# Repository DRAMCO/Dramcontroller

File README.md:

# Dramcontroller
HID controller board design for Engineering Experience 2.
The peripherals with corresponding pins are described below. 
A distinction is made between the on-board peripherals, I2C addresses and sensor slots

## On-board peripherals
| Peripherals | Corresponding GPIO Pin  |
|---|---|
| Buzzer | 2 |
| Vibrator 1 | 12 |
| Vibrator 2 | 5 |
| Debug LED | 13 |
| IO Expender INT | 11 |

## I2C addresses
Four IO expanders connected with the I2C bus control the 7 segment displays, led indicator array and GPIO 3 from every sensor slot. I2C sensors should use always other addresses to prevent collisions during operation.

| IO Expander | Corresponding I2C addres  |
|---|---|
| Sensor slot GPIO 3 | 0x38 |
| Segment display 2 | 0x39 |
| Segment display 1 | 0x3A |
| Led array | 0x3B |

## Sensor slots
### Sensor slot 1
| Peripheral | Pin | Comment |
|---|---|---|
| GPIO 1 | 6 | Digital |
| GPIO 2 | 14  | Digital - Analog |
| GPIO 3 | IO EXP pin 1 | Digital (0b00000001) |
| UART  |  | Serial |
| I2C  |  |  |

### Sensor slot 2
| Peripheral | Pin | Comment |
|---|---|---|
| GPIO 1 | 39 | Digital |
| GPIO 2 | 15  | Digital - Analog |
| GPIO 3 | IO EXP pin 2 | Digital (0b00000010) |
| UART  |  | Serial |
| I2C  |  |  |

### Sensor slot 3
| Peripheral | Pin | Comment |
|---|---|---|
| GPIO 1 | 8 | Digital |
| GPIO 2 | 16  | Digital - Analog |
| GPIO 3 | IO EXP pin 3 | Digital (0b00000100) |
| UART  |  | Serial |
| I2C  |  |  |

### Sensor slot 4
| Peripheral | Pin | Comment |
|---|---|---|
| GPIO 1 | 9 | Digital |
| GPIO 2 | 17  | Digital - Analog |
| GPIO 3 | IO EXP pin 4 | Digital (0b00001000) |
| UART  |  | Serial |
| I2C  |  |  |

### Sensor slot 5
| Peripheral | Pin | Comment |
|---|---|---|
| GPIO 1 | 10 | Digital |
| GPIO 2 | 18  | Digital - Analog |
| GPIO 3 | IO EXP pin 5 | Digital (0b00010000) |
| UART  |  | Serial1 |
| I2C  |  |  |

### Sensor slot 6
| Peripheral | Pin | Comment |
|---|---|---|
| GPIO 1 | 23 | Digital |
| GPIO 2 | 19  | Digital - Analog |
| GPIO 3 | IO EXP pin 6 | Digital (0b00100000) |
| UART  |  | Serial1 |
| I2C  |  |  |

### Sensor slot 7
| Peripheral | Pin | Comment |
|---|---|---|
| GPIO 1 | 24 | Digital |
| GPIO 2 | 4  | Digital - Analog |
| GPIO 3 | IO EXP pin 7 | Digital (0b01000000) |
| UART  |  | Serial1 |
| I2C  |  |  |

### Sensor slot 8
| Peripheral | Pin | Comment |
|---|---|---|
| GPIO 1 | 22 | Digital |
| GPIO 2 | 3  | Digital - Analog |
| GPIO 3 | IO EXP pin 8 | Digital (0b10000000) |
| UART  |  | Serial1 |
| I2C  |  |  |

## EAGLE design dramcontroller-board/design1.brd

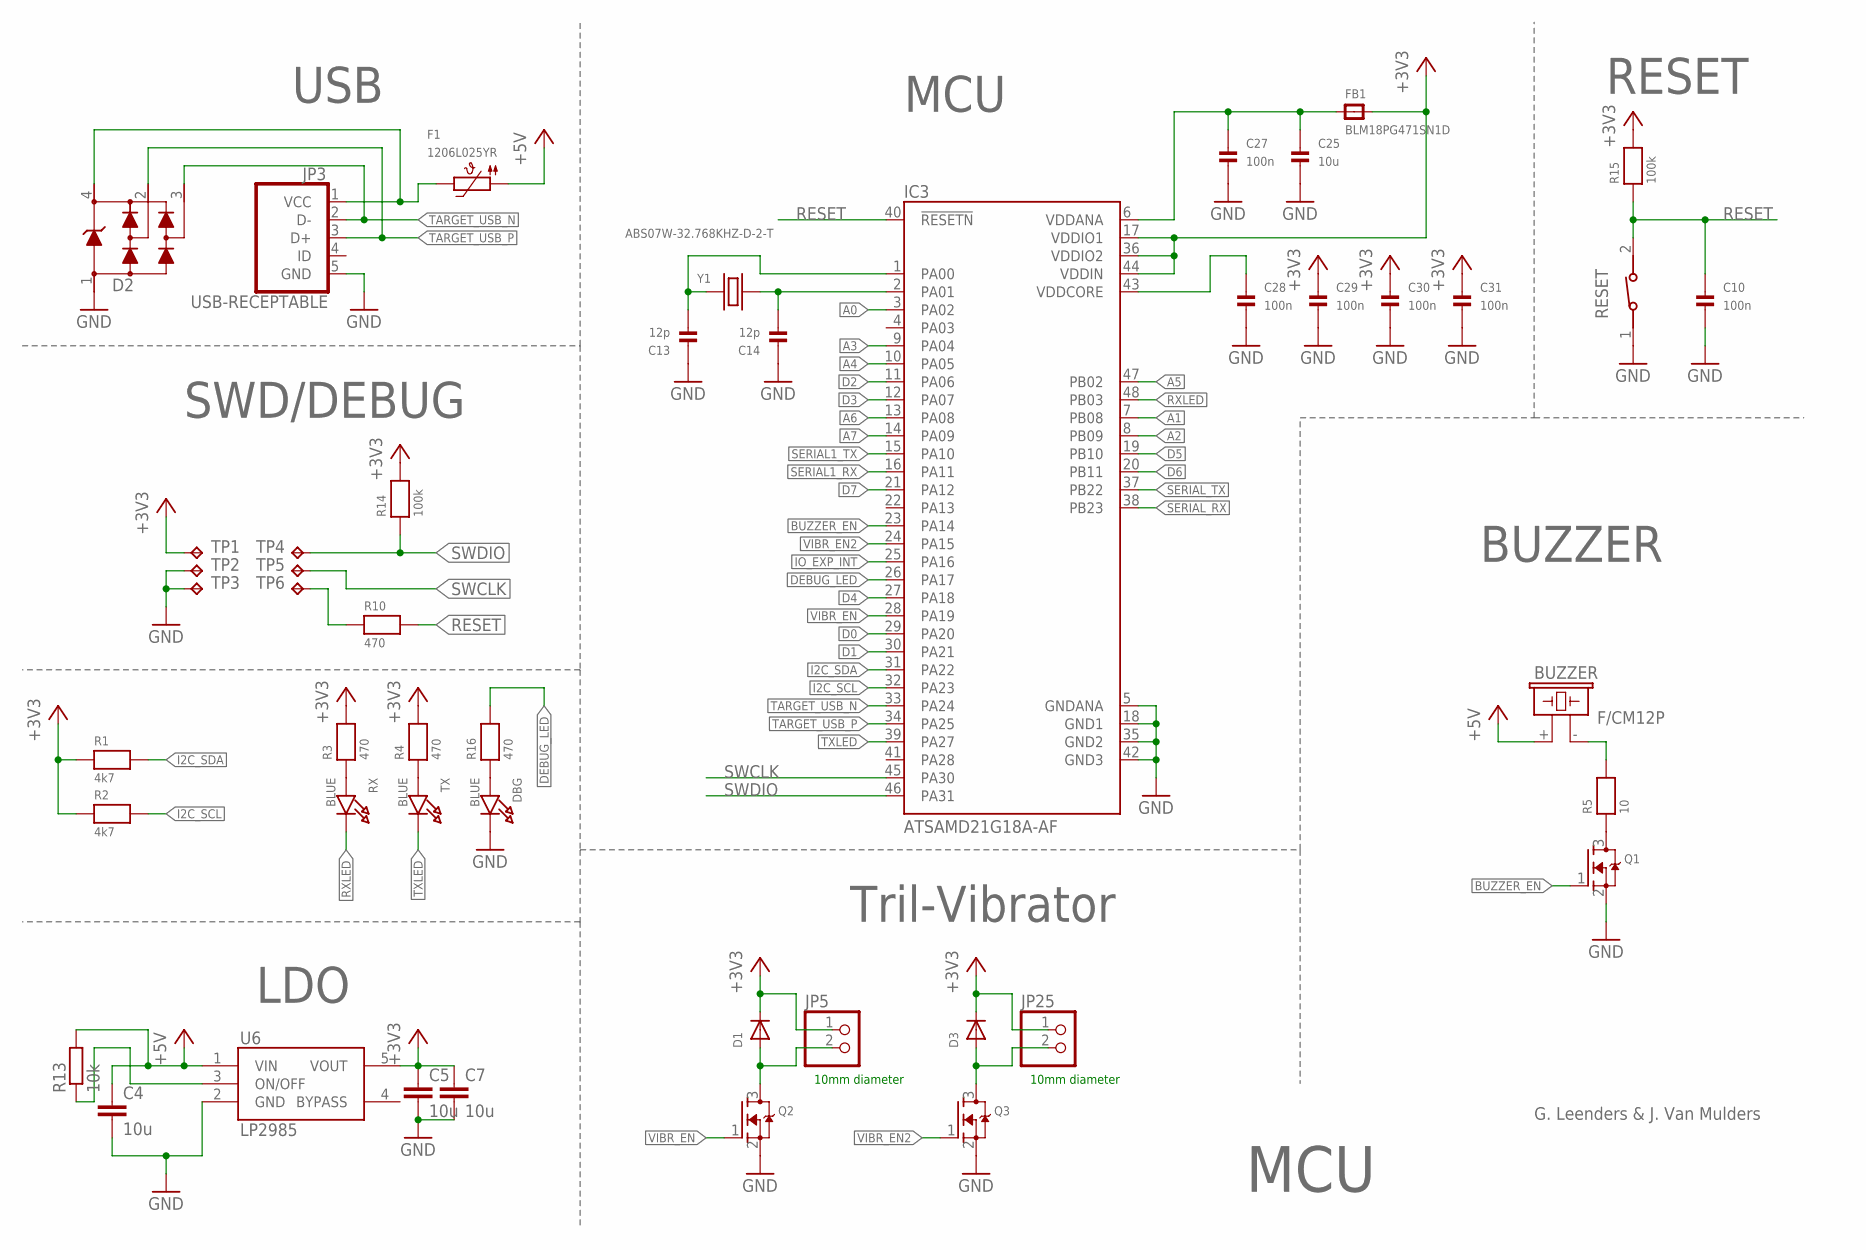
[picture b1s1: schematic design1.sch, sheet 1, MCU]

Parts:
BUZZER: F/CM12P
C4, C5, C7: 10u; C0805
C10, C27, C28, C29, C30, C31: 100n; 0603
C13, C14: 12p; 0603
C25: 10u; 0805
D1, D3: DIODESOD-123; SOD-123
D2: PRTR5V0U2X,215; SOT143B
DBG: BLUE; CHIPLED_0805
F1: 1206L025YR; 1206
FB1: BLM18PG471SN1D; _0603
IC3: ATSAMD21G18A-AF; QFP50P900X900X120-48N
JP3: USB-RECEPTABLE; FCI-10103594-0001LF
JP5, JP25: HEADER-1X2ROUND; 1X02_ROUND
Q1, Q2, Q3: MOSFET-NWIDE; SOT23-WIDE
R1, R2: 4k7; 0603
R3, R4, R10, R16: 470; 0603
R5: 10; 0603
R13: 10k; R0603
R14, R15: 100k; 0603
RESET: 434111043826
RX: BLUE; CHIPLED_0805
TP1, TP2, TP3, TP4, TP5, TP6: TPTP11R; TP11R
TX: BLUE; CHIPLED_0805
U6: LP2985AIM5-3.3; SOT25
Y1: ABS07W-32.768KHZ-D-2-T; XTAL320X150X90

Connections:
+3V3: C5.1, C7.1, C29.1, C30.1, C31.1, D1.C, D3.C, FB1.2, IC3.17 (VDDIO1), IC3.36 (VDDIO2), IC3.44 (VDDIN), JP5.1, JP25.1, R1.1, R2.1, R3.2, R4.2, R14.2, R15.2, TP1.TP, U6.5 (VOUT); also elsewhere on the board
+5V: BUZZER.+ (1), C4.1, F1.1, R13.2, U6.1 (VIN)
A0: IC3.3 (PA02); also elsewhere on the board
A1: IC3.7 (PB08); also elsewhere on the board
A2: IC3.8 (PB09); also elsewhere on the board
A3: IC3.9 (PA04); also elsewhere on the board
A4: IC3.10 (PA05); also elsewhere on the board
A5: IC3.47 (PB02); also elsewhere on the board
A6: IC3.13 (PA08); also elsewhere on the board
A7: IC3.14 (PA09); also elsewhere on the board
BUZZER_EN: IC3.23 (PA14), Q1.1 (G)
D0: IC3.29 (PA20); also elsewhere on the board
D1: IC3.30 (PA21); also elsewhere on the board
D2: IC3.11 (PA06); also elsewhere on the board
D3: IC3.12 (PA07); also elsewhere on the board
D4: IC3.27 (PA18); also elsewhere on the board
D5: IC3.19 (PB10); also elsewhere on the board
D6: IC3.20 (PB11); also elsewhere on the board
D7: IC3.21 (PA12); also elsewhere on the board
DEBUG_LED: IC3.26 (PA17), R16.2
GND: C4.2, C5.2, C7.2, C10.2, C13.1, C14.1, C25.2, C27.2, C28.2, C29.2, C30.2, C31.2, D2.1, DBG.C, IC3.5 (GNDANA), IC3.18 (GND1), IC3.35 (GND2), IC3.42 (GND3), JP3.5 (GND), Q1.2 (S), Q2.2 (S), Q3.2 (S), RESET.1, TP2.TP, TP3.TP, U6.2 (GND); also elsewhere on the board
I2C_SCL: IC3.32 (PA23), R2.2; also elsewhere on the board
I2C_SDA: IC3.31 (PA22), R1.2; also elsewhere on the board
IO_EXP_INT: IC3.25 (PA16); also elsewhere on the board
LDO_EN: R13.1, U6.3 (ON/OFF)
unnamed: R3.1, RX.A
unnamed: R4.1, TX.A
unnamed: BUZZER.- (2), R5.2
unnamed: C28.1, IC3.43 (VDDCORE)
unnamed: Q1.3 (D), R5.1
unnamed: C25.1, C27.1, FB1.1, IC3.6 (VDDANA)
unnamed: D2.4, F1.2, JP3.1 (VCC)
unnamed: D3.A, JP25.2, Q3.3 (D)
unnamed: C13.2, IC3.1 (PA00), Y1.1
unnamed: C14.2, IC3.2 (PA01), Y1.2
unnamed: DBG.A, R16.1
unnamed: R10.1, TP6.TP
unnamed: D1.A, JP5.2, Q2.3 (D)
RESET: C10.1, IC3.40 (!RESETN), R10.2, R15.1, RESET.2
RXLED: IC3.48 (PB03), RX.C
SERIAL1_RX: IC3.16 (PA11); also elsewhere on the board
SERIAL1_TX: IC3.15 (PA10); also elsewhere on the board
SERIAL_RX: IC3.38 (PB23); also elsewhere on the board
SERIAL_TX: IC3.37 (PB22); also elsewhere on the board
SWCLK: IC3.45 (PA30), TP5.TP
SWDIO: IC3.46 (PA31), R14.1, TP4.TP
TARGET_USB_N: D2.3, IC3.33 (PA24), JP3.2 (D-)
TARGET_USB_P: D2.2, IC3.34 (PA25), JP3.3 (D+)
TXLED: IC3.39 (PA27), TX.C
VIBR_EN: IC3.28 (PA19), Q2.1 (G)
VIBR_EN2: IC3.24 (PA15), Q3.1 (G)

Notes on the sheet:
10mm diameter
MCU
G. Leenders & J. Van Mulders
LDO
USB
SWD/DEBUG
RESET
BUZZER
Tril-Vibrator

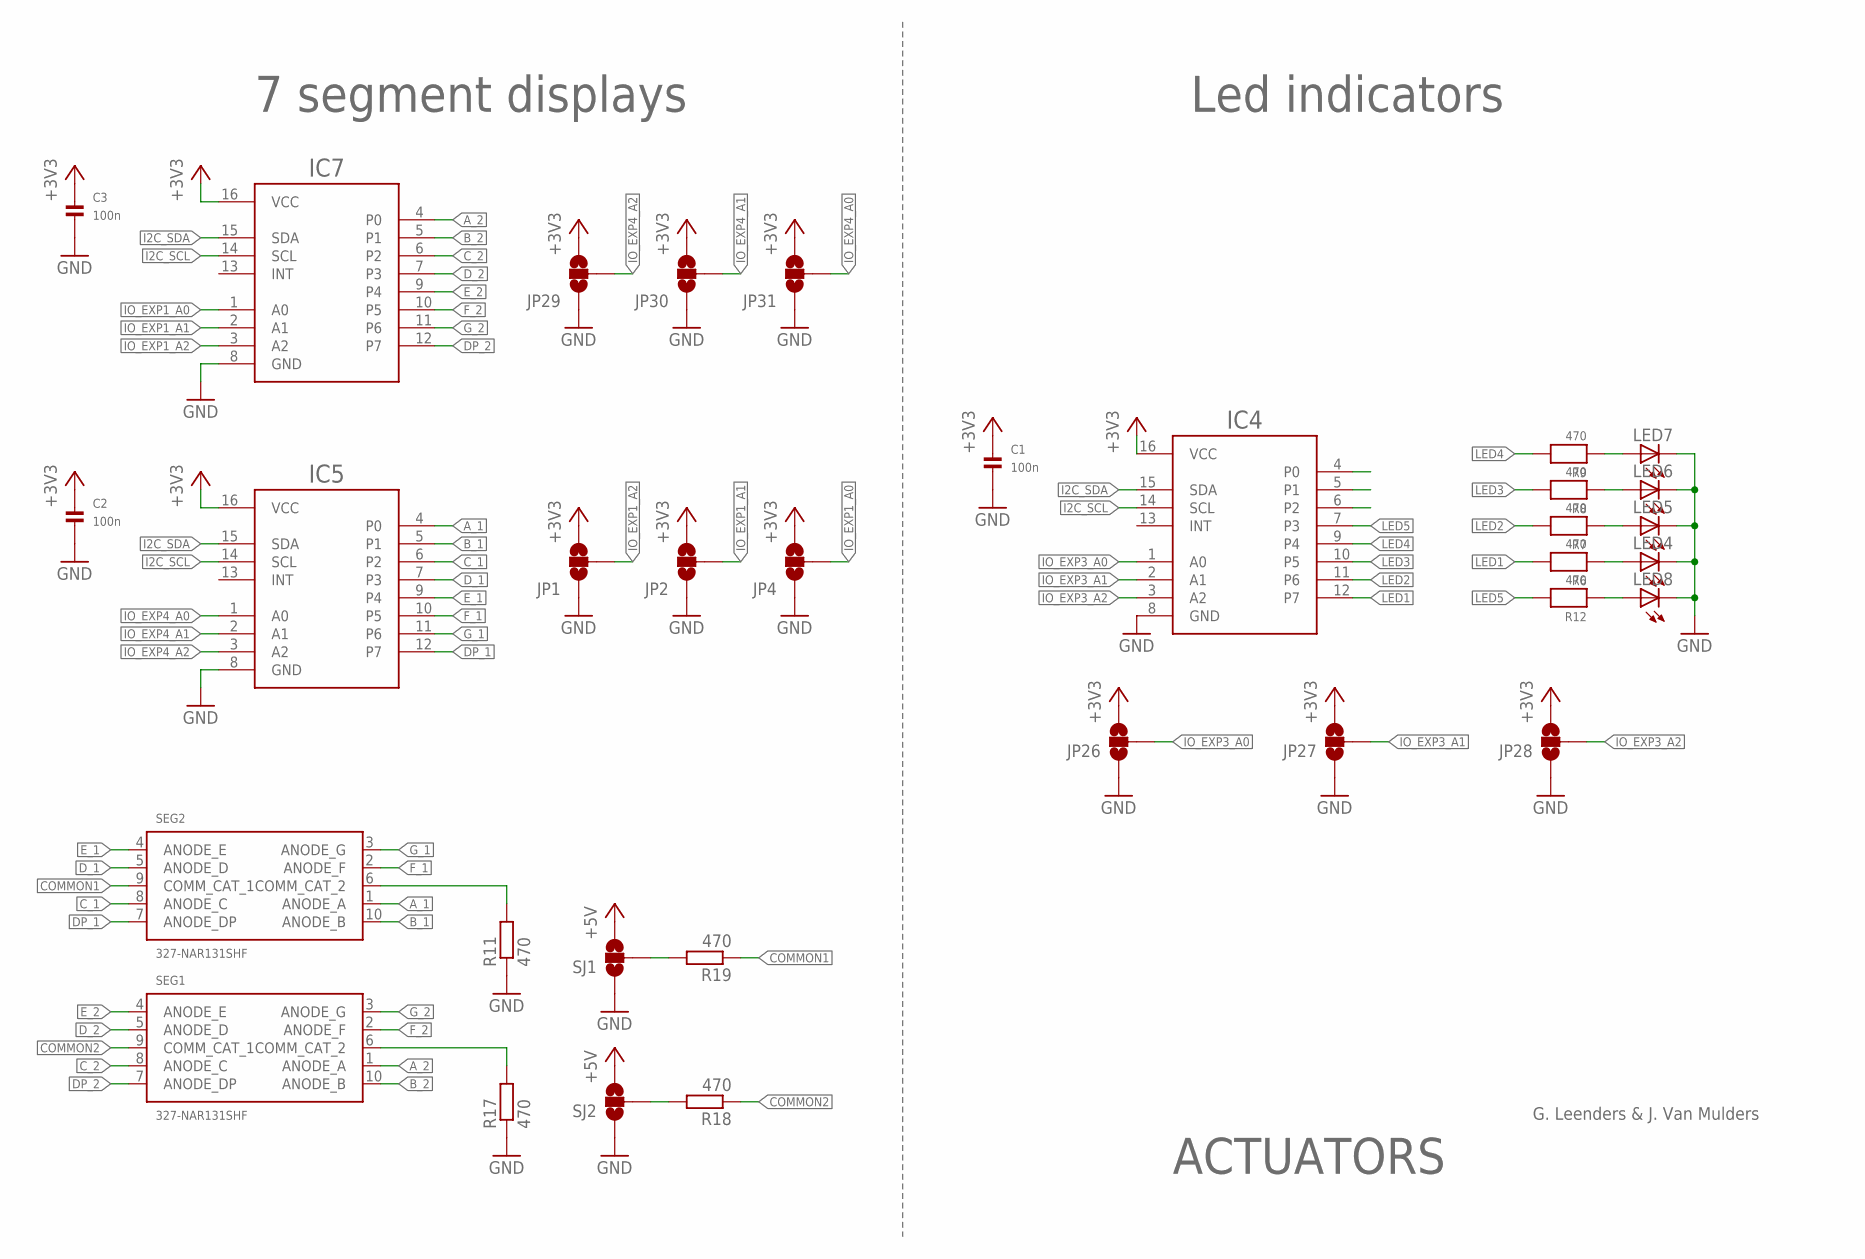
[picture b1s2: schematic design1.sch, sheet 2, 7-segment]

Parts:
C1, C2, C3: 100n; 0603
IC4, IC5, IC7: TCA9554ADBR; SSOP-16
JP1, JP2, JP4, JP26, JP27, JP28, JP29, JP30, JP31: JUMPER-SMT_3_NO_NO-SILK; SMT-JUMPER_3_NO_NO-SILK
LED4, LED5, LED6, LED7, LED8: LED3MM
R6, R7, R8, R9, R12: 470; 0603
R11, R17, R18, R19: 470; R0603
SEG1, SEG2: 327-NAR131SHF; NAR131SH-F
SJ1, SJ2: JUMPER-SMT_3_NO_NO-SILK; SMT-JUMPER_3_NO_NO-SILK

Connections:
+3V3: C1.1, C2.1, C3.1, IC4.16 (VCC), IC5.16 (VCC), IC7.16 (VCC), JP1.3, JP2.3, JP4.3, JP26.3, JP27.3, JP28.3, JP29.3, JP30.3, JP31.3, SJ1.3, SJ2.3; also elsewhere on the board
A_1: IC5.4 (P0), SEG2.1 (ANODE_A)
A_2: IC7.4 (P0), SEG1.1 (ANODE_A)
B_1: IC5.5 (P1), SEG2.10 (ANODE_B)
B_2: IC7.5 (P1), SEG1.10 (ANODE_B)
COMMON1: R19.1, SEG2.9 (COMM_CAT_1)
COMMON2: R18.1, SEG1.9 (COMM_CAT_1)
C_1: IC5.6 (P2), SEG2.8 (ANODE_C)
C_2: IC7.6 (P2), SEG1.8 (ANODE_C)
DP_1: IC5.12 (P7), SEG2.7 (ANODE_DP)
DP_2: IC7.12 (P7), SEG1.7 (ANODE_DP)
D_1: IC5.7 (P3), SEG2.5 (ANODE_D)
D_2: IC7.7 (P3), SEG1.5 (ANODE_D)
E_1: IC5.9 (P4), SEG2.4 (ANODE_E)
E_2: IC7.9 (P4), SEG1.4 (ANODE_E)
F_1: IC5.10 (P5), SEG2.2 (ANODE_F)
F_2: IC7.10 (P5), SEG1.2 (ANODE_F)
GND: C1.2, C2.2, C3.2, IC4.8 (GND), IC5.8 (GND), IC7.8 (GND), JP1.1, JP2.1, JP4.1, JP26.1, JP27.1, JP28.1, JP29.1, JP30.1, JP31.1, LED4.K (C), LED5.K (C), LED6.K (C), LED7.K (C), LED8.K (C), R11.1, R17.1, SJ1.1, SJ2.1; also elsewhere on the board
G_1: IC5.11 (P6), SEG2.3 (ANODE_G)
G_2: IC7.11 (P6), SEG1.3 (ANODE_G)
I2C_SCL: IC4.14 (SCL), IC5.14 (SCL), IC7.14 (SCL); also elsewhere on the board
I2C_SDA: IC4.15 (SDA), IC5.15 (SDA), IC7.15 (SDA); also elsewhere on the board
IO_EXP1_A0: IC7.1 (A0), JP4.2
IO_EXP1_A1: IC7.2 (A1), JP2.2
IO_EXP1_A2: IC7.3 (A2), JP1.2
IO_EXP3_A0: IC4.1 (A0), JP26.2
IO_EXP3_A1: IC4.2 (A1), JP27.2
IO_EXP3_A2: IC4.3 (A2), JP28.2
IO_EXP4_A0: IC5.1 (A0), JP31.2
IO_EXP4_A1: IC5.2 (A1), JP30.2
IO_EXP4_A2: IC5.3 (A2), JP29.2
LED1: IC4.12 (P7), R6.2
LED2: IC4.11 (P6), R7.2
LED3: IC4.10 (P5), R8.2
LED4: IC4.9 (P4), R9.2
LED5: IC4.7 (P3), R12.2
unnamed: R17.2, SEG1.6 (COMM_CAT_2)
unnamed: LED8.A, R12.1
unnamed: LED4.A, R6.1
unnamed: LED5.A, R7.1
unnamed: LED6.A, R8.1
unnamed: LED7.A, R9.1
unnamed: R11.2, SEG2.6 (COMM_CAT_2)
unnamed: R19.2, SJ1.2
unnamed: R18.2, SJ2.2

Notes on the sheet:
ACTUATORS
7 segment displays
Led indicators
G. Leenders & J. Van Mulders

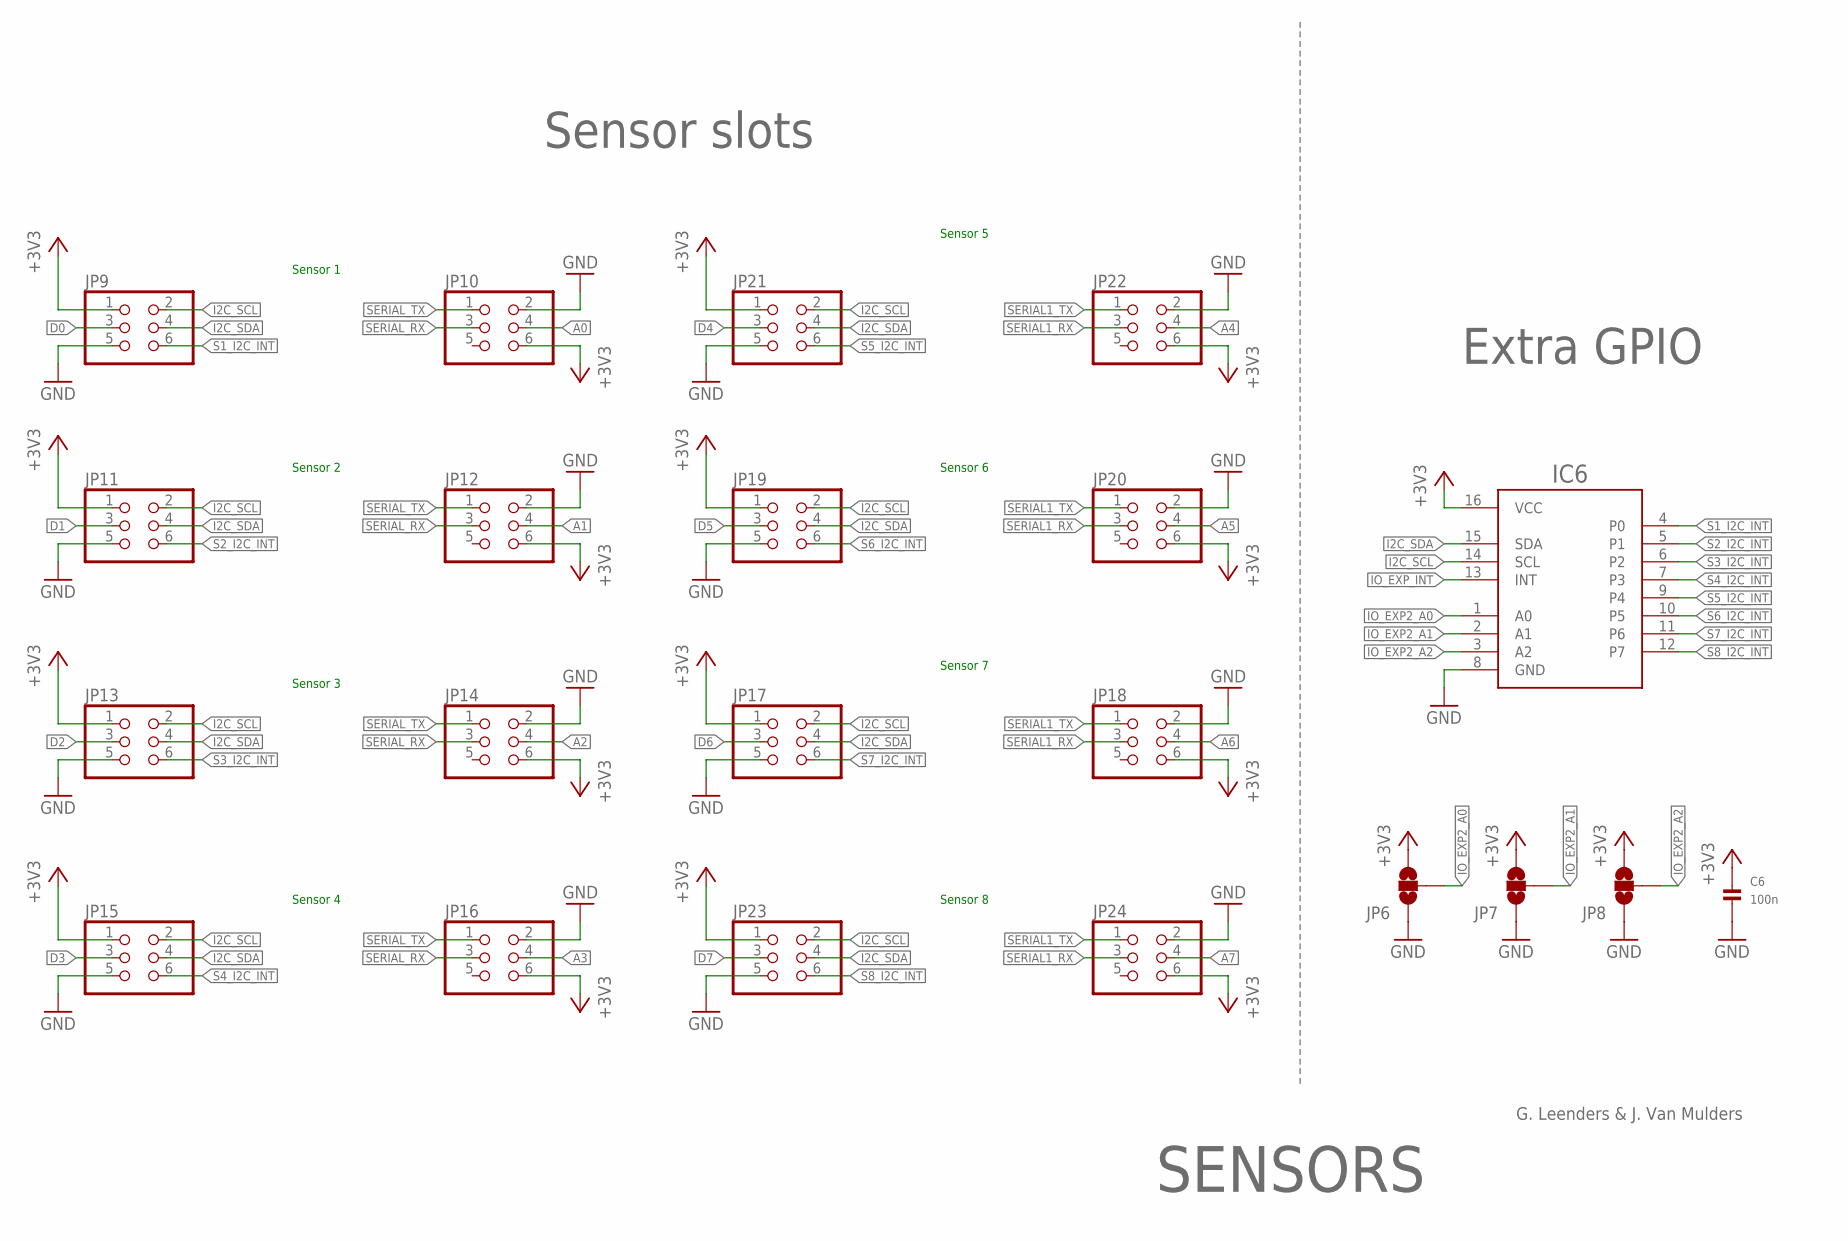
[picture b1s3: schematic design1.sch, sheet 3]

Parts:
C6: 100n; 0603
IC6: TCA9554ADBR; SSOP-16
JP6, JP7, JP8: JUMPER-SMT_3_NO_NO-SILK; SMT-JUMPER_3_NO_NO-SILK
JP9, JP10, JP11, JP12, JP13, JP14, JP15, JP16, JP17, JP18, JP19, JP20, JP21, JP22, JP23, JP24: HEADER-2X3; 2X03_ROUND_70MIL

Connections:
+3V3: C6.1, IC6.16 (VCC), JP6.3, JP7.3, JP8.3, JP9.1, JP10.6, JP11.1, JP12.6, JP13.1, JP14.6, JP15.1, JP16.6, JP17.1, JP18.6, JP19.1, JP20.6, JP21.1, JP22.6, JP23.1, JP24.6; also elsewhere on the board
A0: JP10.4; also elsewhere on the board
A1: JP12.4; also elsewhere on the board
A2: JP14.4; also elsewhere on the board
A3: JP16.4; also elsewhere on the board
A4: JP22.4; also elsewhere on the board
A5: JP20.4; also elsewhere on the board
A6: JP18.4; also elsewhere on the board
A7: JP24.4; also elsewhere on the board
D0: JP9.3; also elsewhere on the board
D1: JP11.3; also elsewhere on the board
D2: JP13.3; also elsewhere on the board
D3: JP15.3; also elsewhere on the board
D4: JP21.3; also elsewhere on the board
D5: JP19.3; also elsewhere on the board
D6: JP17.3; also elsewhere on the board
D7: JP23.3; also elsewhere on the board
GND: C6.2, IC6.8 (GND), JP6.1, JP7.1, JP8.1, JP9.5, JP10.2, JP11.5, JP12.2, JP13.5, JP14.2, JP15.5, JP16.2, JP17.5, JP18.2, JP19.5, JP20.2, JP21.5, JP22.2, JP23.5, JP24.2; also elsewhere on the board
I2C_SCL: IC6.14 (SCL), JP9.2, JP11.2, JP13.2, JP15.2, JP17.2, JP19.2, JP21.2, JP23.2; also elsewhere on the board
I2C_SDA: IC6.15 (SDA), JP9.4, JP11.4, JP13.4, JP15.4, JP17.4, JP19.4, JP21.4, JP23.4; also elsewhere on the board
IO_EXP2_A0: IC6.1 (A0), JP6.2
IO_EXP2_A1: IC6.2 (A1), JP7.2
IO_EXP2_A2: IC6.3 (A2), JP8.2
IO_EXP_INT: IC6.13 (INT); also elsewhere on the board
S1_I2C_INT: IC6.4 (P0), JP9.6
S2_I2C_INT: IC6.5 (P1), JP11.6
S3_I2C_INT: IC6.6 (P2), JP13.6
S4_I2C_INT: IC6.7 (P3), JP15.6
S5_I2C_INT: IC6.9 (P4), JP21.6
S6_I2C_INT: IC6.10 (P5), JP19.6
S7_I2C_INT: IC6.11 (P6), JP17.6
S8_I2C_INT: IC6.12 (P7), JP23.6
SERIAL1_RX: JP18.3, JP20.3, JP22.3, JP24.3; also elsewhere on the board
SERIAL1_TX: JP18.1, JP20.1, JP22.1, JP24.1; also elsewhere on the board
SERIAL_RX: JP10.3, JP12.3, JP14.3, JP16.3; also elsewhere on the board
SERIAL_TX: JP10.1, JP12.1, JP14.1, JP16.1; also elsewhere on the board

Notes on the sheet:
Sensor 5
Sensor 6
Sensor 7
Sensor 8
Sensor 1
Sensor 2
Sensor 3
Sensor 4
SENSORS
G. Leenders & J. Van Mulders
Sensor slots
Extra GPIO

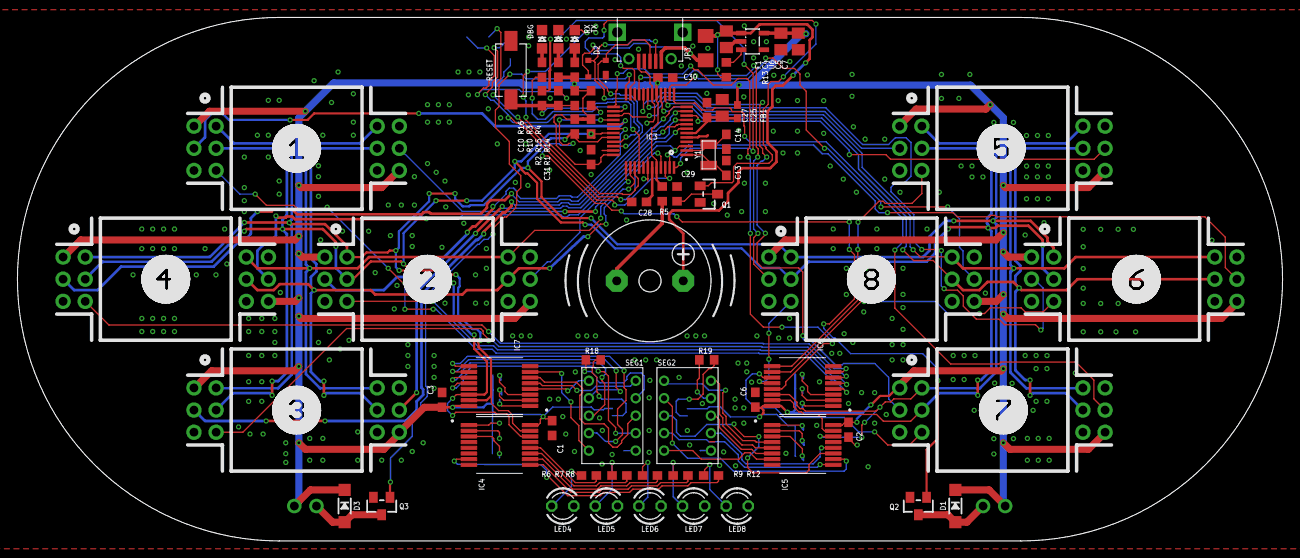
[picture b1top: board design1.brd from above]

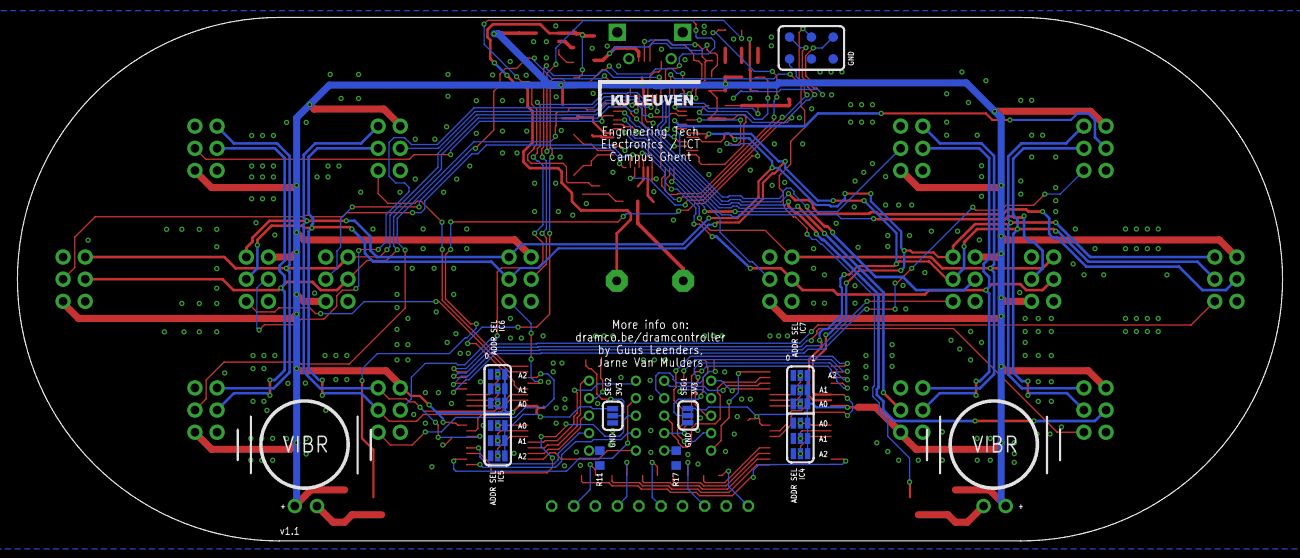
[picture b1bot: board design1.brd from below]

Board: 2 copper layers, 145.0 x 60.0 mm, 101 parts (40 on the bottom side), 103 nets.

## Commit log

2022-02-17 Update I2C addresses

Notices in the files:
parts and their libraries:
microbuilder: This work is placed in the public domain, and may be freely used for commercial and non-commercial work with the following conditions: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
SparkFun-Jumpers: Licensing: Creative Commons ShareAlike 4.0 International - https://creativecommons.org/licenses/by-sa/4.0
